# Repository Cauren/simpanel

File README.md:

# simpanel
Flight Simulator autopilot and general switch panel.

This is very much work-in-progress; it works, but the build process for the components requires manual steps and programming. The device is a functioning HID providing 37 buttons and four linear encoders exposed as relative dials; those should be usable as-is in well-written software.

The leds and numeric displays are controlled by HID output reports which most flight simulators are unable to use directly, but there are software tools to interface simulator panels with flight simulators that can do the required; in particular SPAD.neXt (https://spadnext.com) has support for the panels and will interface with at least FSX, MSFS2020, X-Plane and Prepar3D.

The hardware is in a decent state and the CADs for the PCBoard are included.  Do note there isn't a proper BOM for assembly right now, you'll have to inventory the schematics for the list of parts.

If you really like the idea and want to fiddle with it, you almost certainly want to drop me an email for help and guidance for now.

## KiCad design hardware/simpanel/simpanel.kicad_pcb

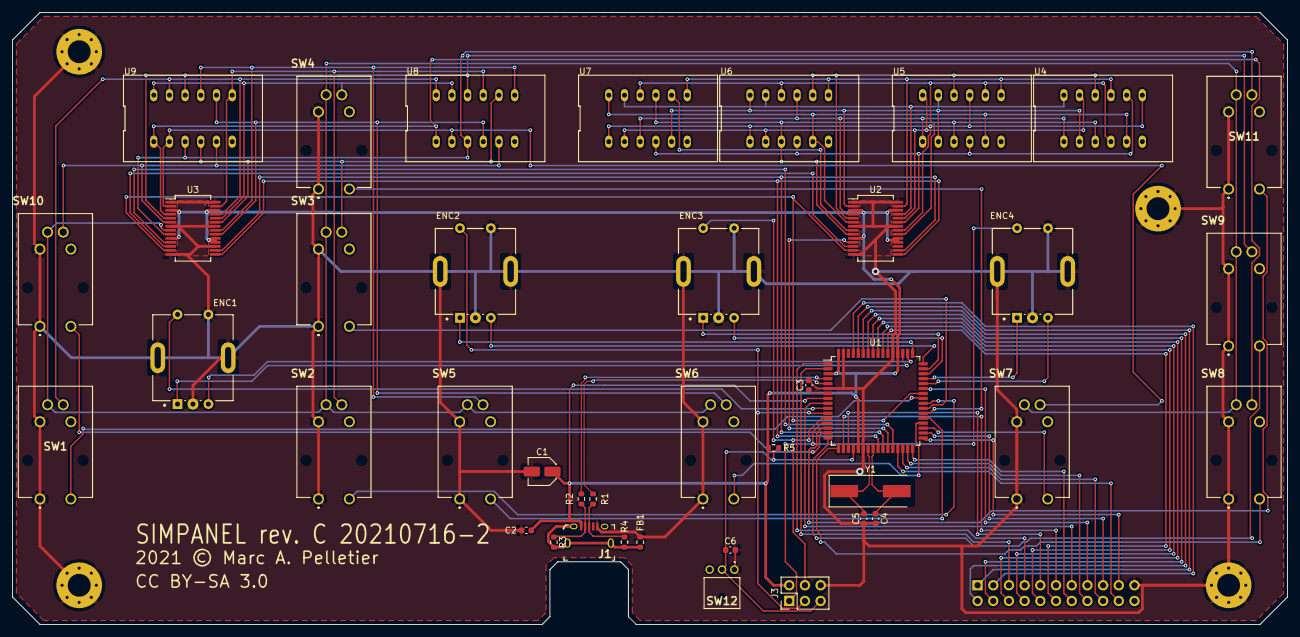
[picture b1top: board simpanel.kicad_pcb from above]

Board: 2 copper layers, 206.4 x 99.1 mm, 45 parts (1 on the bottom side), 84 nets.

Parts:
C1: 47µf; C_Elec_4x5.4
C2, C6: 100nf; C_0603_1608Metric
C3: 1µf; C_0603_1608Metric
C4, C5: 22pf; C_0603_1608Metric
ENC1, ENC2, ENC3, ENC4: PEC11R-4220F-S0024; PEC11R
FB1: BLM21; R_0603_1608Metric
H1, H2, H3, H4: MountingHole_Pad; MountingHole_3.7mm_Pad_Via
J1: U-F-M5DW-Y-2; USB_Micro_B_Female_10118194-0001LF
J2: Conn_2Rows-21Pins; PinHeader_2x11_P2.54mm_Vertical
J3: ISP; PinHeader_2x03_P2.54mm_Vertical
R1, R2: 22; R_0603_1608Metric
R3, R4: CG0603MLC-05E; R_0603_1608Metric
R5: 10k; R_0603_1608Metric
SW1, SW2, SW3, SW4, SW5, SW6, SW7, SW8, SW9, SW10, SW11: B3J-2100; B3J2100
SW12: SW_Push; XKB5858WC
U1: AT90USB1286-AU; TQFP-64_14x14mm_P0.8mm
U2, U3: AS1130-BSST; SSOP-28_5.3x10.2mm_P0.65mm
U4, U5, U6, U7, U8, U9: SLR0363DWC1BD
Y1: 16MHz; Crystal_SMD_HC49-SD

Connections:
/CSA0: U2.25, U4.12, U5.11, U6.11, U7.11
/CSA1: U2.27, U4.9, U5.7, U6.7, U7.7
/CSA2: U2.23, U4.8, U5.4, U6.4, U7.4
/CSA3: U2.24, U4.11, U5.12, U6.2, U7.2
/CSA4: U2.21, U4.7, U5.9, U6.1, U7.1
/CSA5: U2.20, U4.4, U5.8, U6.10, U7.10
/CSA6: U2.2, U4.2, U5.2, U6.12, U7.5
/CSA7: U2.4, U4.1, U5.1, U6.9, U7.3
/CSA8: U2.5, U4.10, U5.10, U6.8
/CSA9: U2.6, U4.5, U5.5, U6.5, U7.12
/CSA10: U2.9, U4.3, U5.3, U6.3, U7.9
/CSA11: U2.8, U7.8
/CSB0: SW1.A1, U3.25, U8.12, U9.11
/CSB1: SW2.A1, U3.27, U8.9, U9.7
/CSB2: SW3.A1, U3.23, U8.8, U9.4
/CSB3: SW4.A1, U3.24, U8.11, U9.12
/CSB4: SW5.A1, U3.21, U8.7, U9.9
/CSB5: SW6.A1, U3.20, U8.4, U9.8
/CSB6: SW7.A1, U3.2, U8.2, U9.2
/CSB7: SW8.A1, U3.4, U8.1, U9.1
/CSB8: SW9.A1, U3.5, U8.10, U9.10
/CSB9: SW10.A1, U3.6, U8.5, U9.5
/CSB10: SW11.A1, U3.9, U8.3, U9.3
/CSB11: SW1.K1, SW2.K1, SW3.K1, SW4.K1, SW5.K1, SW6.K1, SW7.K1, SW8.K1, SW9.K1, SW10.K1, SW11.K1, U3.8
/D+: R1.1, U1.5
/D-: R2.1, U1.4
/ENC1A: ENC1.A, U1.51
/ENC1B: ENC1.B, U1.50
/ENC1S: ENC1.1, U1.10
/ENC2A: ENC2.A, U1.49
/ENC2B: ENC2.B, U1.48
/ENC2S: ENC2.1, J3.3, U1.11
/ENC3A: ENC3.A, U1.47
/ENC3B: ENC3.B, U1.46
/ENC3S: ENC3.1, J3.4, U1.12
/ENC4A: ENC4.A, U1.45
/ENC4B: ENC4.B, U1.44
/ENC4S: ENC4.1, J3.1, U1.13
/IRQA: U1.27, U2.11
/IRQB: U1.28, U3.11
/PB4: SW11.3, U1.14
/PB5: SW10.3, U1.15
/PB6: SW9.3, U1.16
/PB7: SW8.3, U1.17
/PC0: SW7.3, U1.35
/PC1: SW6.3, U1.36
/PC2: SW5.3, U1.37
/PC3: SW4.3, U1.38
/PC4: SW3.3, U1.39
/PC5: SW2.3, U1.40
/PC6: SW1.3, U1.41
/PC7: U1.42, U2.13, U3.13
/PD4: J2.20, U1.29
/PD5: J2.18, U1.30
/PD6: J2.16, U1.31
/PD7: J2.14, U1.32
/PE0: J2.19, U1.33
/PE1: J2.17, U1.34
/PE2: J2.15, U1.43
/PE3: J2.13, U1.9
/PE4: J2.11, U1.18
/PE5: J2.9, U1.19
/PE6: J2.7, U1.1
/PE7: J2.5, U1.2
/PF0: J2.3, U1.61
/PF1: J2.1, U1.60
/PF2: J2.2, U1.59
/PF3: J2.4, U1.58
/PF4: J2.6, U1.57
/PF5: J2.8, U1.56
/PF6: J2.10, U1.55
/PF7: J2.12, U1.54
/RESET: C6.1, J3.5, R5.2, SW12.2, U1.20
/SCL: U1.25, U2.15, U3.15
/SDA: U1.26, U2.16, U3.16
/SHIELD: FB1.2, J1.SH, R3.2, R4.2
/SYNC: U2.12, U3.12
/UCAP: C3.1, U1.7
/UD+: J1.3, R1.2, R4.1
/UD-: J1.2, R2.2, R3.1
/XTAL+: C4.1, U1.24, Y1.2
/XTAL-: C5.1, U1.23, Y1.1
GND: C1.2, C2.2, C3.2, C4.2, C5.2, C6.2, ENC1.2, ENC1.3, ENC1.4, ENC1.C, ENC2.2, ENC2.3, ENC2.4, ENC2.C, ENC3.2, ENC3.3, ENC3.4, ENC3.C, ENC4.2, ENC4.3, ENC4.4, ENC4.C, FB1.1, H1.1, H2.1, H3.1, H4.1, J1.5, J2.21, J3.6, SW1.1, SW1.2, SW2.1, SW2.2, SW3.1, SW3.2, SW4.1, SW4.2, SW5.1, SW5.2, SW6.1, SW6.2, SW7.1, SW7.2, SW8.1, SW8.2, SW9.1, SW9.2, SW10.1, SW10.2, SW11.1, SW11.2, SW12.1, U1.6, U1.22, U1.53, U1.63, U2.1, U2.7, U2.14, U2.22, U2.28, U3.1, U3.7, U3.14, U3.17, U3.22, U3.28
VCC: C1.1, C2.1, J1.1, J3.2, R5.1, U1.3, U1.8, U1.21, U1.52, U1.64, U2.3, U2.10, U2.18, U2.19, U2.26, U3.3, U3.10, U3.18, U3.19, U3.26

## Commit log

2020-12-23 Push of existing code
2020-12-23 Reorg a bit
2020-12-23 Add better string support, descriptor improvements, "real" USB IDs
2020-12-23 Add PCB CAD
2020-12-23 Forgotten file to ignore
2020-12-23 Retroactive ignore
2020-12-23 Separate casing CAD from PCB
2020-12-23 Added I-have-a-driver mode for dumb software
    Some things are to dumb to speak proper HID, and will miss updates
    because they can't grok all the data types.
    Yes, MSFS2020, I'm talking to you.
2020-12-28 Added AS1130 driver code
2020-12-31 Added MSFS-side code
    SimpanelModule goes in, SimpanelConnect goes out
2020-12-31 A few more chars, and nicer boot
2021-01-02 Moar better, works now.
    No more hardcoded
2021-01-04 Make README reflect current state a little better
2021-01-22 All switches need pull-up with the revised hardware
2021-07-20 Rev C board runs on AT90USB
2021-07-20 WIP update for rev A. board (rev C update not yet in place)
2021-07-20 Cleanup
2021-07-20 +.gitignore
2021-07-20 Rev C
2021-07-20 README tweaks because Rev C
2021-07-28 Update to go pure HID (serial port still there for debug)
2021-08-04 Module rewrite to use (a) pure HID (b) better factoring
    This moves the logic out of the WASM module, leaving only the piping there
    to allow the external driver to exvaluate gauge expressions.
2021-08-09 Remove serial console crap now that the device is pure HID
2021-08-11 With that, firmware is pretty much finished. Version 1.0.0
2021-08-11 Update README now that the device is pure HID
2021-08-11 WIP tweaks
2021-08-11 Make the number of live expressions in GaugeConnect properly dynamic
2021-08-11 Explain what GaugeConnect _is_
2021-08-12 GaugeConnect is now... "good enough". Version 1.0.0.
2021-08-13 Make the plug not eat a CPU
2021-08-14 Add Notify Icon and status popout
2021-08-15 First stab at WebView2 GUI initialization
    Just tries to load a 'Hello World' into WebView2
    No errors, but also no web view. Not sure what's wrong yet.
    SDK will be installed via NuGet in the Visual Studio project.
    Runtime must be installed manually:
    https://developer.microsoft.com/en-us/microsoft-edge/webview2/
2021-08-16 Still no web view, but got label in systray popup
2021-08-16 Setting visibility helps the webview :D
2021-08-24 Use UTF-8 for the html file
2021-08-25 Use Windows 10 runtime for JSON messaging
    Currently not yet hooked up to the internal events for
    detecting devices or planes etc and doesn't actually send
    events to the web view yet, so nothing is filled out.
    But it's getting closer. ;)
2021-08-25 Don't show heading if no heading is set
2021-08-27 Add .gitignore for build artifacts
2021-08-27 Fix a nasty object initialization bug and add power status for avionics
2021-08-27 ... or not. Wrong bug.
2021-08-27 Also blank when no sim or exiting
2021-08-28 Sensible defaults for all switches
2021-09-10 Prototype for RS firmware
2021-09-12 radiostack firmware prototype (fakes it with X11)
2021-12-12 Make config loadable and saveable
2021-12-25 Support simvars directly, and k-events (incorrectly)
2023-12-15 Update README.md to mention SPAD.neXt support
    This makes the SimpanelConnect and the WASM wedge module obsolete.

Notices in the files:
hardware/simpanel/simpanel.kicad_pcb:
CC-BY-SA 3.0
Copyright © 2020 Marc A. Pelletier
2021 © Marc A. Pelletier
